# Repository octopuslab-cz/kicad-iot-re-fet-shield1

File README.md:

# kicad-iot-re-fet-shield1

octopusLab KiCad project - relay and MOS-FET (for PWM)

---
## version 0.1 

- 7805
- 2x 100uF/20V
- 3x Led + resistors 1k

---

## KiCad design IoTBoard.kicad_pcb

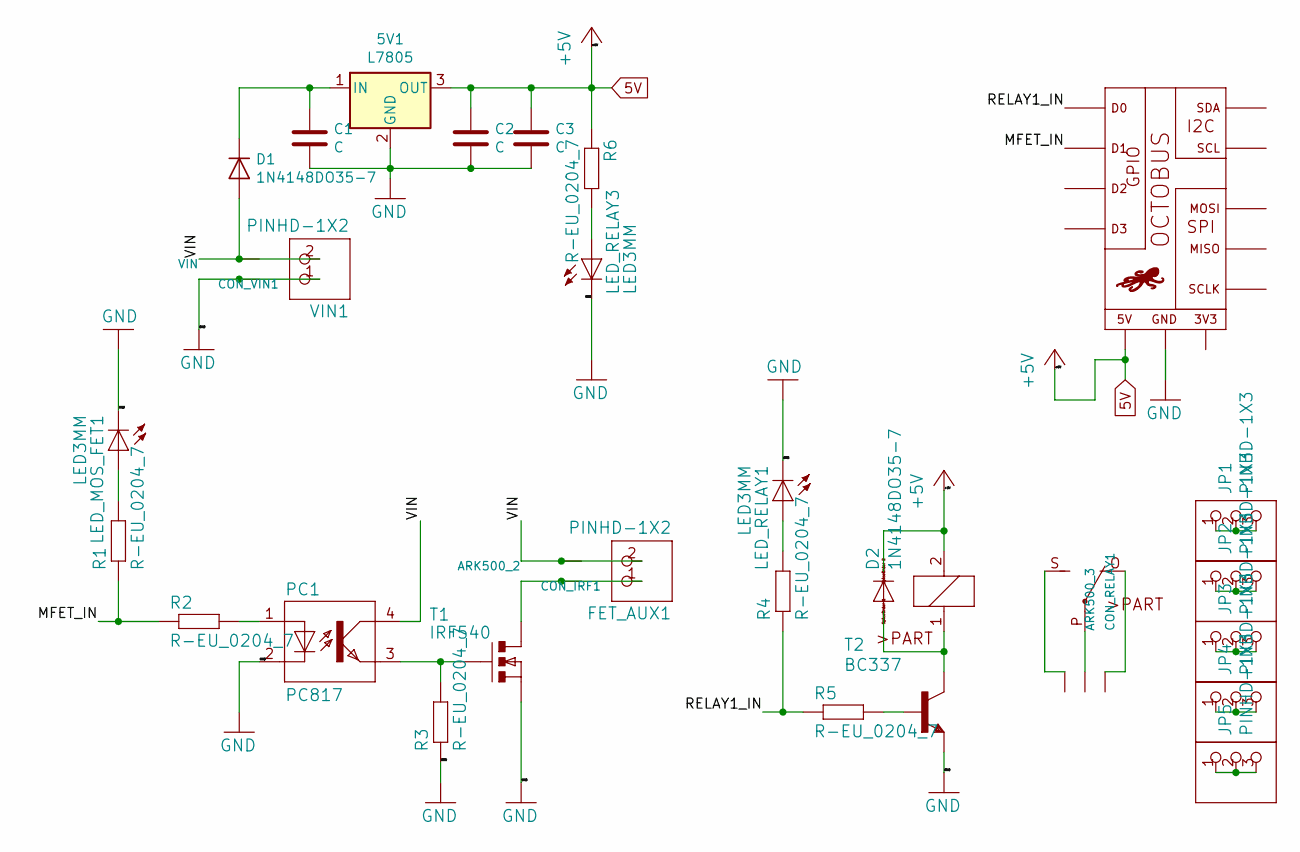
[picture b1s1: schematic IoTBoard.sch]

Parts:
5V1: L7805; TO-220S
C1, C2: C; CP_Radial_D5.0mm_P2.50mm
C3: C; C_Rect_L7.0mm_W2.5mm_P5.00mm
CON_IRF1: ARK500_2
CON_RELAY1: ARK500_3
CON_VIN1: VIN; ARK500_2
D1: 1N4148DO35-7; D_DO-35_SOD27_P7.62mm_Horizontal
D2: 1N4148DO35-7; DO35-7
FET_AUX1: PINHD-1X2; 1X02
JP1, JP2, JP3, JP4, JP5: PINHD-1X3; PinHeader_1x03_P2.54mm_Vertical
LED_MOS_FET1: LED3MM
LED_RELAY1, LED_RELAY3: LED3MM
PC1: PC817; DIL04
R1, R2, R3, R4, R5, R6: R-EU_0204_7; 0204_7
RELAY1: G5LE
T1: IRF540; TO-220S
T2: BC337; TO92
U1: EDUshiled1-eagle-import_OCTOBUSFULL; OCTOBUS
VIN1: PINHD-1X2; 1X02

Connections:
5V: 5V1.3 (OUT), C2.1, C3.1, D2.C, R6.1, RELAY1.2, U1.5V, U1.5V_AUX (5V); also elsewhere on the board
/MFET_IN: R1.1, R2.1, U1.D1, U1.D1_AUX (D1)
/RELAY1_IN: R4.1, R5.1, U1.D0, U1.D0_AUX (D0)
/VIN: CON_IRF1.2, CON_VIN1.2, D1.2 (A), FET_AUX1.2, PC1.4 (COL), VIN1.2
GND: 5V1.2 (GND), C1.2, C2.2, C3.2, CON_VIN1.1, LED_MOS_FET1.K (C), LED_RELAY1.K (C), LED_RELAY3.K (C), PC1.2 (C), R3.1, T1.3 (S), T2.1 (E), U1.GND, U1.GND_2 (GND), U1.GND_AUX (GND), VIN1.1
unnamed: 5V1.1 (IN), C1.1, D1.1 (K)
unnamed: CON_IRF1.1, FET_AUX1.1, T1.2 (D)
unnamed 7: CON_RELAY1.1, RELAY1.O; also elsewhere on the board
unnamed 8: CON_RELAY1.2, RELAY1.P; also elsewhere on the board
unnamed 9: CON_RELAY1.3, RELAY1.S; also elsewhere on the board
unnamed 10: D2.A, RELAY1.1, T2.3 (C); also elsewhere on the board
unnamed: JP1.1, JP1.2, JP1.3
unnamed: JP2.1, JP2.2, JP2.3
unnamed: JP3.1, JP3.2, JP3.3
unnamed: JP4.1, JP4.2, JP4.3
unnamed: JP5.1, JP5.2, JP5.3
unnamed: LED_MOS_FET1.A, R1.2
unnamed: LED_RELAY1.A, R4.2
unnamed: LED_RELAY3.A, R6.2
unnamed: PC1.1 (A), R2.2
unnamed: PC1.3 (EMIT), R3.2, T1.1 (G)
unnamed: R5.2, T2.2 (B)
unnamed: U1.3V3, U1.3V3_2 (3V3), U1.3V3_AUX (3V3)
unnamed: U1.D2, U1.D2_AUX (D2)
unnamed: U1.D3, U1.D3_AUX (D3)

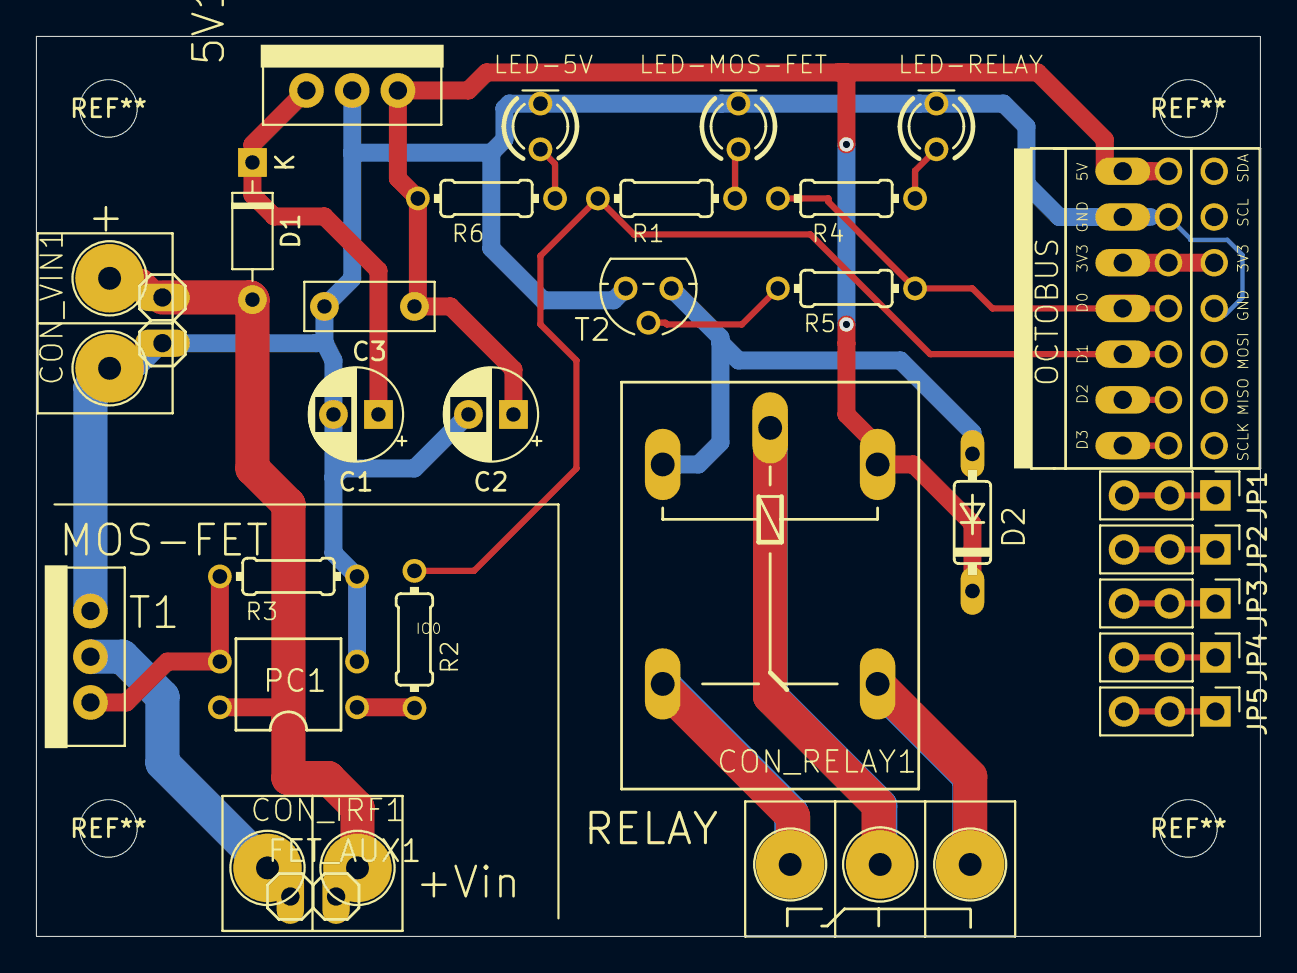
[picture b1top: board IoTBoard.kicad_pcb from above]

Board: 2 copper layers, 68.0 x 50.0 mm, 30 parts (0 on the bottom side), 25 nets.

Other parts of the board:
RELAY: G5LE

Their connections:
5V: RELAY.2; also elsewhere on the board
unnamed 7: RELAY.O; also elsewhere on the board
unnamed 8: RELAY.P; also elsewhere on the board
unnamed 9: RELAY.S; also elsewhere on the board
unnamed 10: RELAY.1; also elsewhere on the board

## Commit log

2020-06-25 initial files
2020-06-26 typo
2020-06-27 photos
